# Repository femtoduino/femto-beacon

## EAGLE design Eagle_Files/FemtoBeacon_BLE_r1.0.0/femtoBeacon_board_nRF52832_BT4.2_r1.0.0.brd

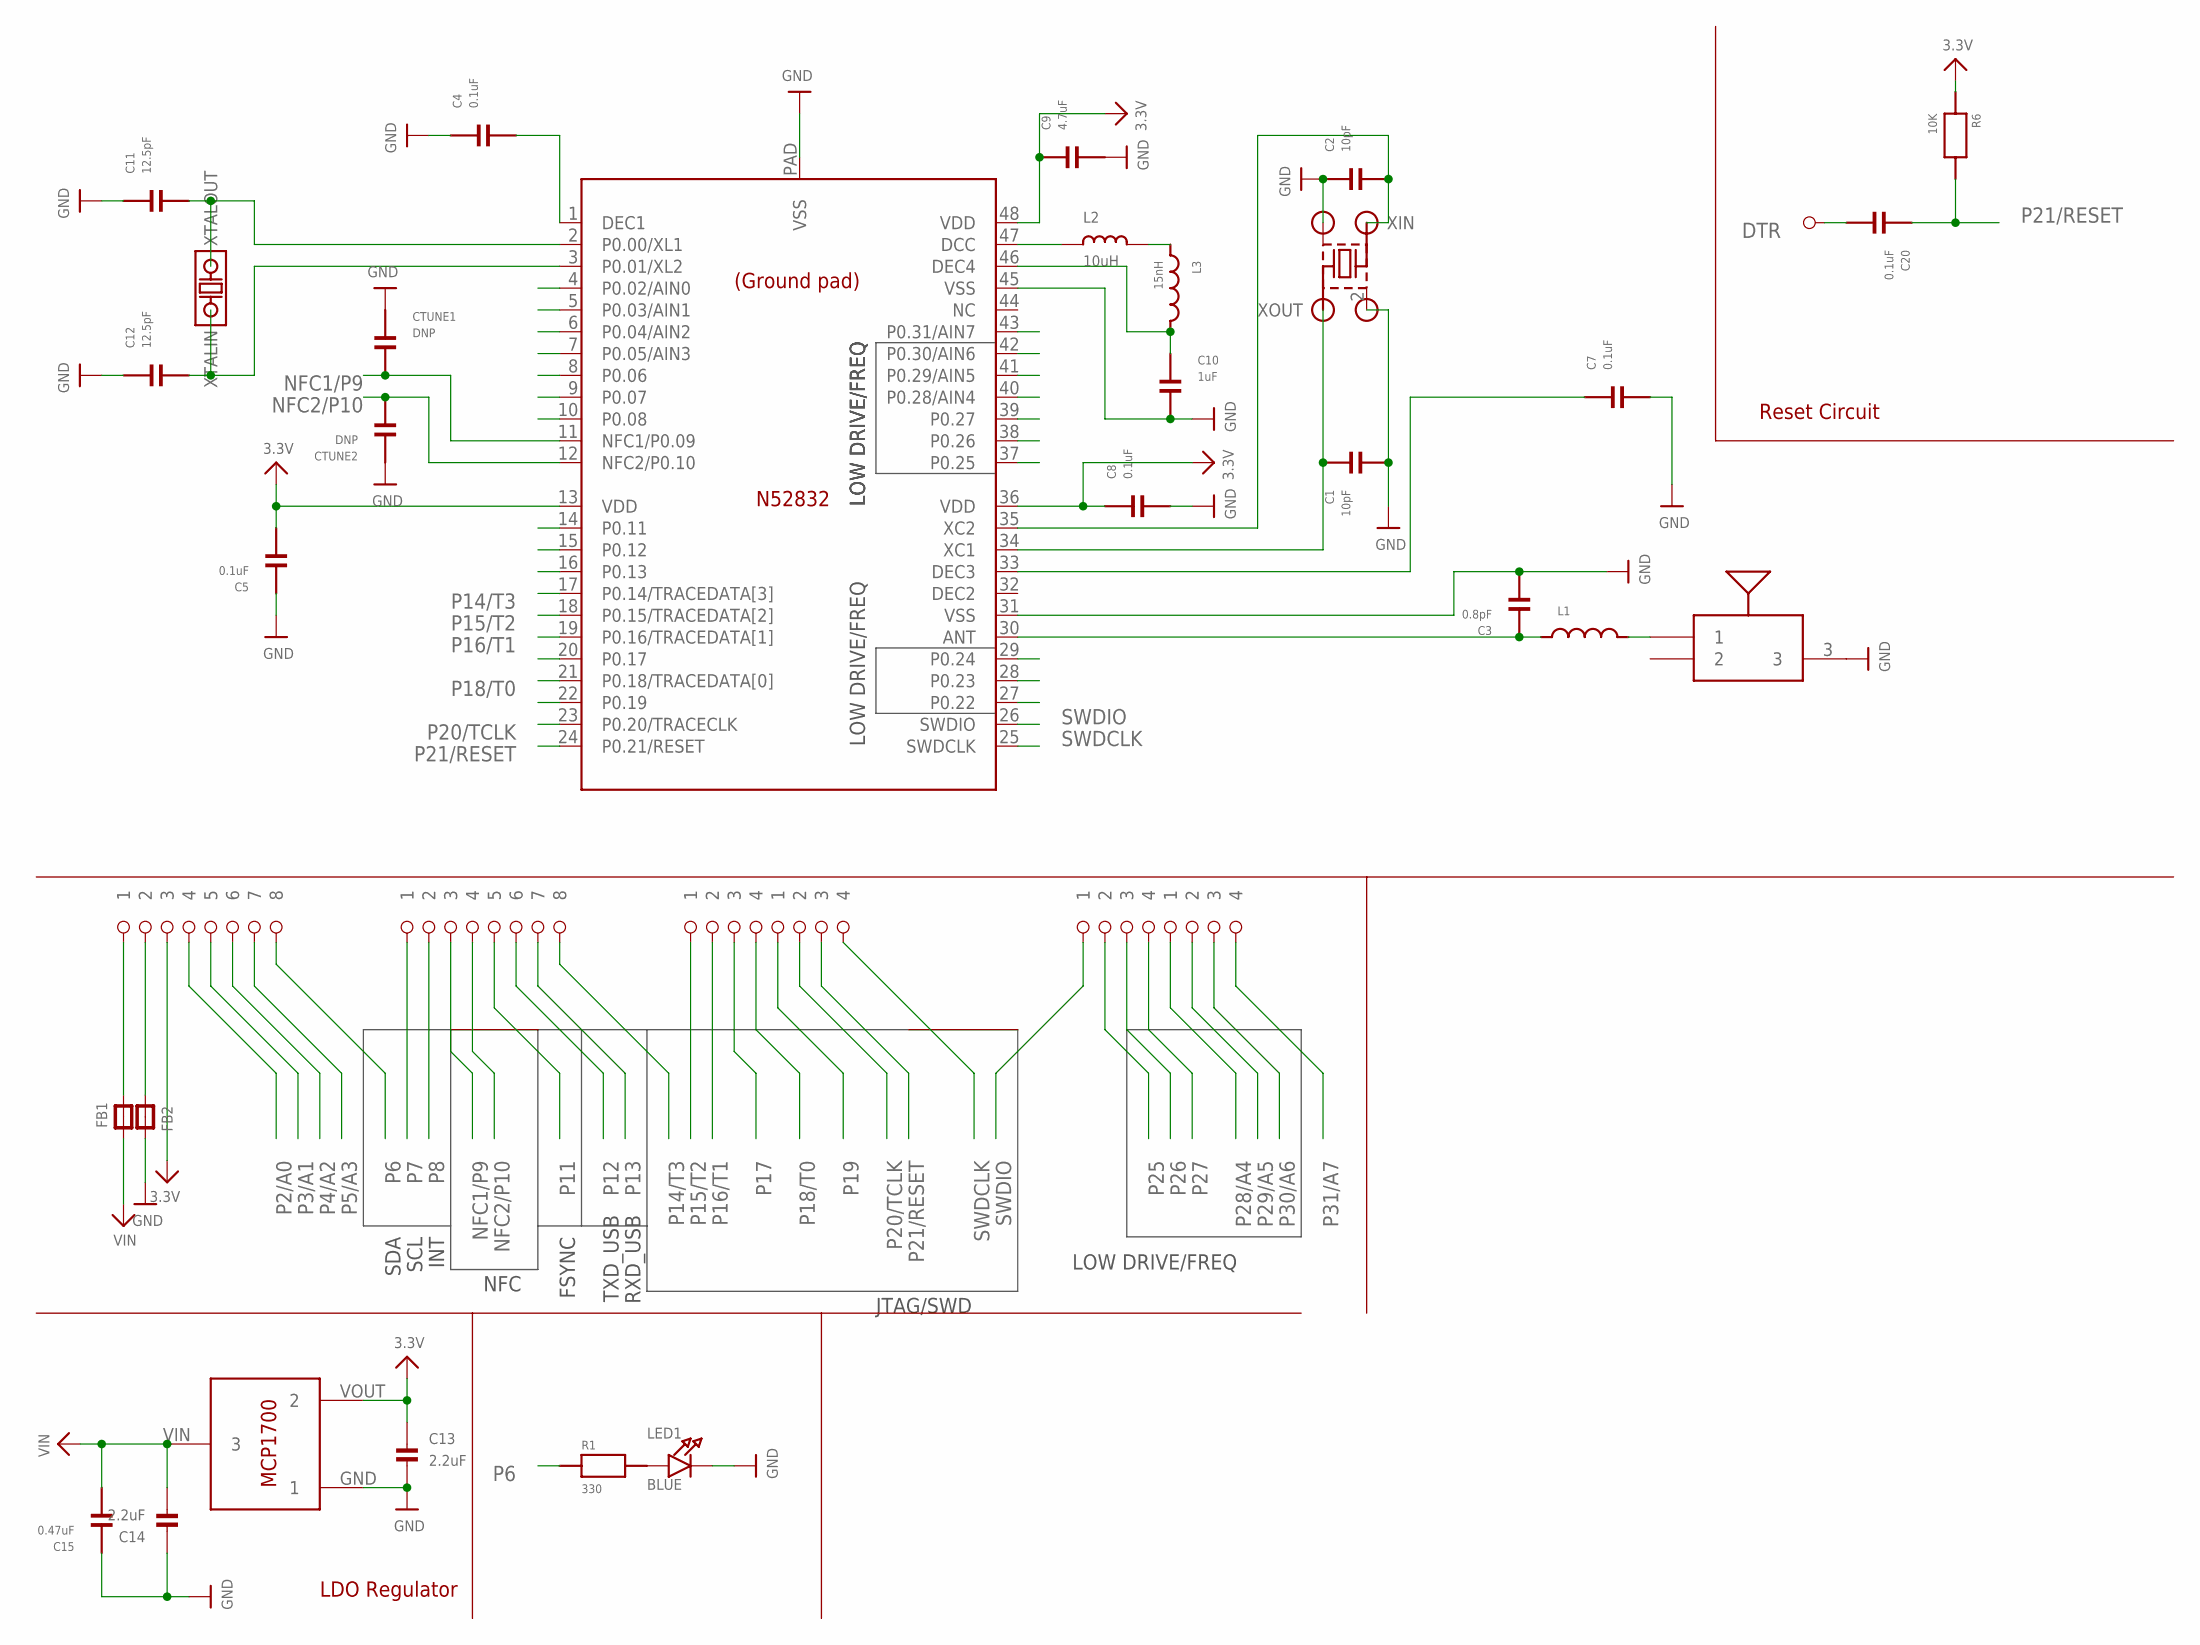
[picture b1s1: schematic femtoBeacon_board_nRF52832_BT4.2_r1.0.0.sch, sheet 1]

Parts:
ANTBAR: PULSE_ANT_2.4GHZ; ANT_BAR
C1, C2: 10pF; PART
C3: 0.8pF; PART
C4, C5, C7, C8, C20: 0.1uF; PART
C9: 4.7uF; PART
C10: 1uF; PART
C11, C12: 12.5pF; PART
C13, C14: 2.2uF; _0402MP
C15: 0.47uF; PART
CTUNE1, CTUNE2: DNP; PART
FB1, FB2: FERRITE_0603MP; _0603MP
IC1: NRF52832_QFN48; QFN48
L1: INDUCTOR_FIXED_0201; PART
L2: 10uH; _0603MP
L3: 15nH; PART
LED1: BLUE; CHIPLED_0603_NOOUTLINE
PIN4: 1X1_ROUND
PINS1, PINS2: 1X8_ROUND
PINS3A, PINS3B, PINS4A, PINS4B: 1X4_ROUND
R1: 330; PART
R6: 10K; PART
U$4: MCP1700T-3302E/TT
U$53: ABS06-107-32.768KHZ-T
XTAL: 32MHz; ABM11

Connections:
3.3V: C5.2, C8.1, C9.1, C13.1, IC1.13 (VDD), IC1.36 (VDD), IC1.48 (VDD), PINS1.P$3 (3), R6.1, U$4.VOUT (2); also elsewhere on the board
DTR: C20.2, PIN4.P$1
GND: ANTBAR.3, C1.2, C2.1, C3.2, C4.1, C5.1, C7.2, C8.2, C9.2, C10.2, C11.1, C12.1, C13.2, C14.1, C15.1, CTUNE1.1, CTUNE2.1, FB2.2, IC1.31 (VSS), IC1.45 (VSS), IC1.PAD (VSS), LED1.C, U$4.GND (1), XTAL.2 (GND), XTAL.4 (GND); also elsewhere on the board
unnamed: C4.2, IC1.1 (DEC1)
unnamed: L2.2, L3.1
unnamed: IC1.47 (DCC), L2.1
unnamed: C7.1, IC1.33 (DEC3)
unnamed: FB2.1, PINS1.P$2 (2)
unnamed: C10.1, IC1.46 (DEC4), L3.2
unnamed: LED1.A, R1.2
unnamed: FB1.2, PINS1.P$1 (1)
unnamed: C3.1, IC1.30 (ANT), L1.1
NFC1/P9: CTUNE1.2, IC1.11 (NFC1/P0.09), PINS2.P$3 (3)
NFC2/P10: CTUNE2.2, IC1.12 (NFC2/P0.10), PINS2.P$4 (4)
P0/XIN32: C11.2, IC1.2 (P0.00/XL1), U$53.2 (XTALOUT)
P1/XOUT32: C12.2, IC1.3 (P0.01/XL2), U$53.1 (XTALIN)
P2/A0: IC1.4 (P0.02/AIN0), PINS1.P$4 (4)
P3/A1: IC1.5 (P0.03/AIN1), PINS1.P$5 (5)
P4/A2: IC1.6 (P0.04/AIN2), PINS1.P$6 (6)
P5/A3: IC1.7 (P0.05/AIN3), PINS1.P$7 (7)
P6: IC1.8 (P0.06), PINS1.P$8 (8), R1.1; also elsewhere on the board
P7: IC1.9 (P0.07), PINS2.P$1 (1); also elsewhere on the board
P8: IC1.10 (P0.08), PINS2.P$2 (2); also elsewhere on the board
P11: IC1.14 (P0.11), PINS2.P$5 (5); also elsewhere on the board
P12: IC1.15 (P0.12), PINS2.P$6 (6)
P13: IC1.16 (P0.13), PINS2.P$7 (7)
P14/T3: IC1.17 (P0.14/TRACEDATA[3]), PINS2.P$8 (8)
P15/T2: IC1.18 (P0.15/TRACEDATA[2]), PINS3A.P$1 (1)
P16/T1: IC1.19 (P0.16/TRACEDATA[1]), PINS3A.P$2 (2)
P17: IC1.20 (P0.17), PINS3A.P$3 (3)
P18/T0: IC1.21 (P0.18/TRACEDATA[0]), PINS3A.P$4 (4)
P19: IC1.22 (P0.19), PINS3B.P$1 (1)
P20/TCLK: IC1.23 (P0.20/TRACECLK), PINS3B.P$2 (2)
P21/RESET: C20.1, IC1.24 (P0.21/RESET), PINS3B.P$3 (3), R6.2
P22: IC1.27 (P0.22)
P23: IC1.28 (P0.23)
P24: IC1.29 (P0.24)
P25: IC1.37 (P0.25), PINS4A.P$2 (2)
P26: IC1.38 (P0.26), PINS4A.P$3 (3)
P27: IC1.39 (P0.27), PINS4A.P$4 (4)
P28/A4: IC1.40 (P0.28/AIN4), PINS4B.P$1 (1)
P29/A5: IC1.41 (P0.29/AIN5), PINS4B.P$2 (2)
P30/A6: IC1.42 (P0.30/AIN6), PINS4B.P$3 (3)
P31/A7: IC1.43 (P0.31/AIN7), PINS4B.P$4 (4)
RF: ANTBAR.1, L1.2
SWDCLK: IC1.25 (SWDCLK), PINS3B.P$4 (4)
SWDIO: IC1.26 (SWDIO), PINS4A.P$1 (1)
VIN: C14.2, C15.2, FB1.1, U$4.VIN (3)
XIN: C1.1, IC1.34 (XC1), XTAL.3 (XOUT)
XOUT: C2.2, IC1.35 (XC2), XTAL.1 (XIN)

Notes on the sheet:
LOW DRIVE/FREQ
SDA
SCL
INT
FSYNC
TXD_USB
RXD_USB
Reset Circuit
LDO Regulator
JTAG/SWD
NFC

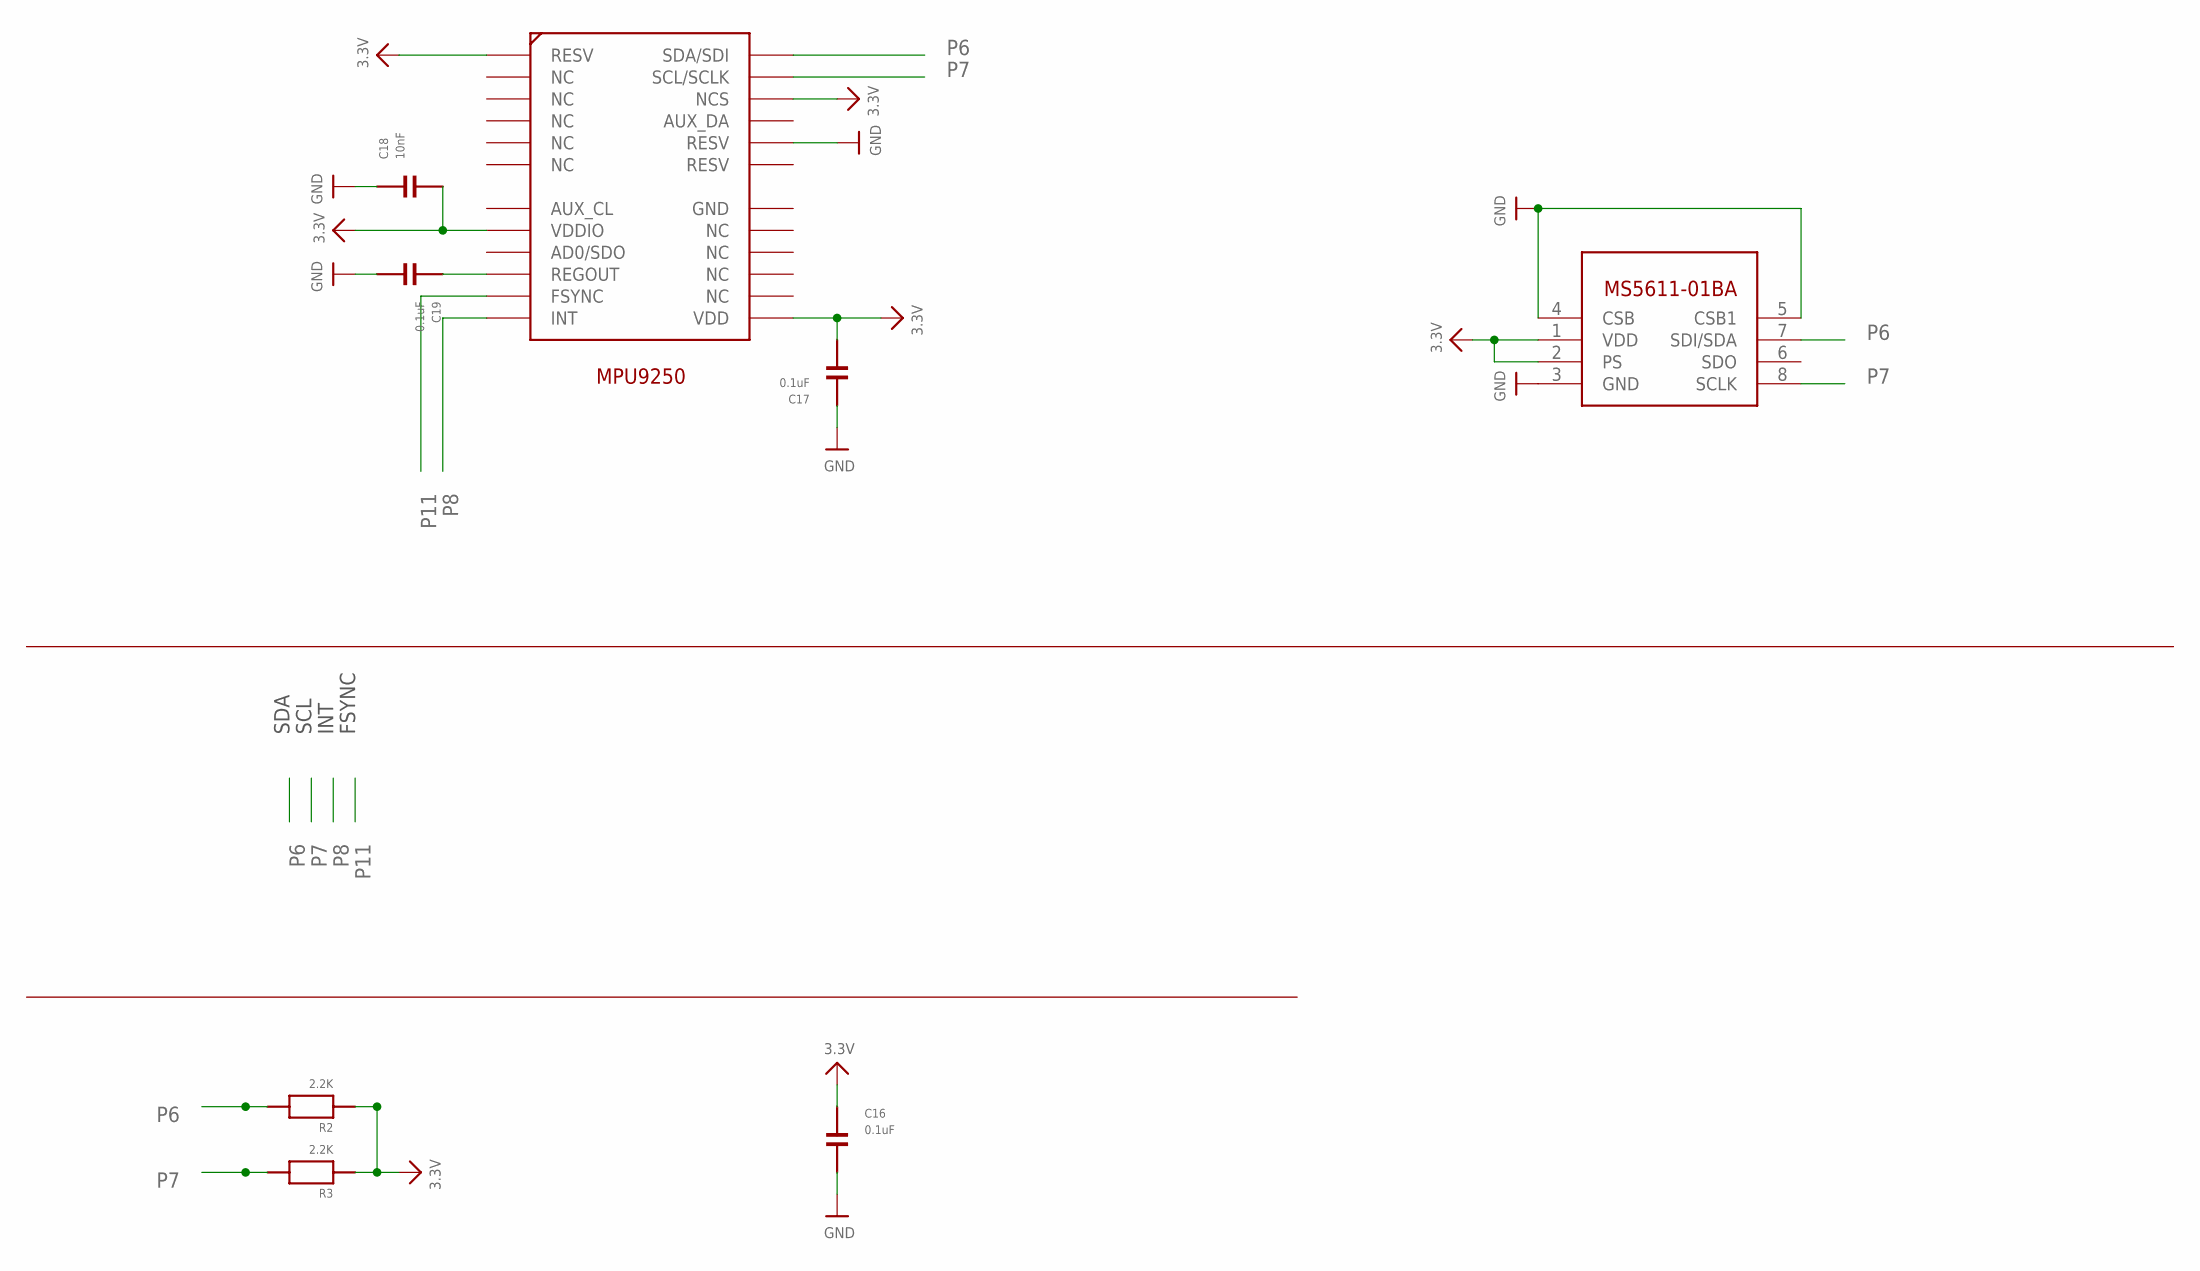
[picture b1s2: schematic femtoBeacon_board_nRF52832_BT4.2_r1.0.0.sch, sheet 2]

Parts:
BARO1: MS5611-01BA03
C16, C17, C19: 0.1uF; PART
C18: 10nF; PART
IMU1: MPU-9250; QFN_3X3MM
R2, R3: 2.2K; PART

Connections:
3.3V: BARO1.1 (VDD), BARO1.2 (PS), C16.1, C17.2, C18.2, IMU1.P$1 (RESV), IMU1.P$8 (VDDIO), IMU1.P$13 (VDD), IMU1.P$22 (NCS), R2.1, R3.1; also elsewhere on the board
GND: BARO1.3 (GND), BARO1.4 (CSB), BARO1.5 (CSB1), C16.2, C17.1, C18.1, C19.2, IMU1.P$20 (RESV); also elsewhere on the board
P6: BARO1.7 (SDI/SDA), IMU1.P$24 (SDA/SDI), R2.2; also elsewhere on the board
P7: BARO1.8 (SCLK), IMU1.P$23 (SCL/SCLK), R3.2; also elsewhere on the board
P8: IMU1.P$12 (INT); also elsewhere on the board
P11: IMU1.P$11 (FSYNC); also elsewhere on the board
REGOUT: C19.1, IMU1.P$10 (REGOUT)

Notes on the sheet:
MPU9250
SDA
SCL
INT
FSYNC

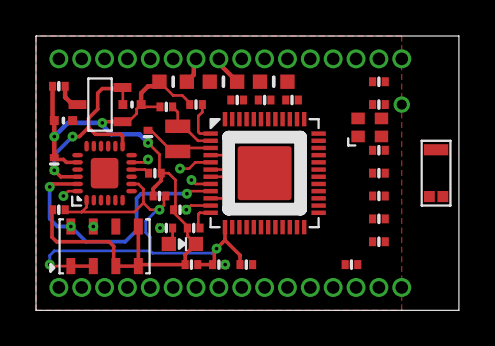
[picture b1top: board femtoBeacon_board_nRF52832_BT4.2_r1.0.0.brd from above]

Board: 4 copper layers, 23.5 x 15.2 mm, 45 parts (0 on the bottom side), 48 nets.

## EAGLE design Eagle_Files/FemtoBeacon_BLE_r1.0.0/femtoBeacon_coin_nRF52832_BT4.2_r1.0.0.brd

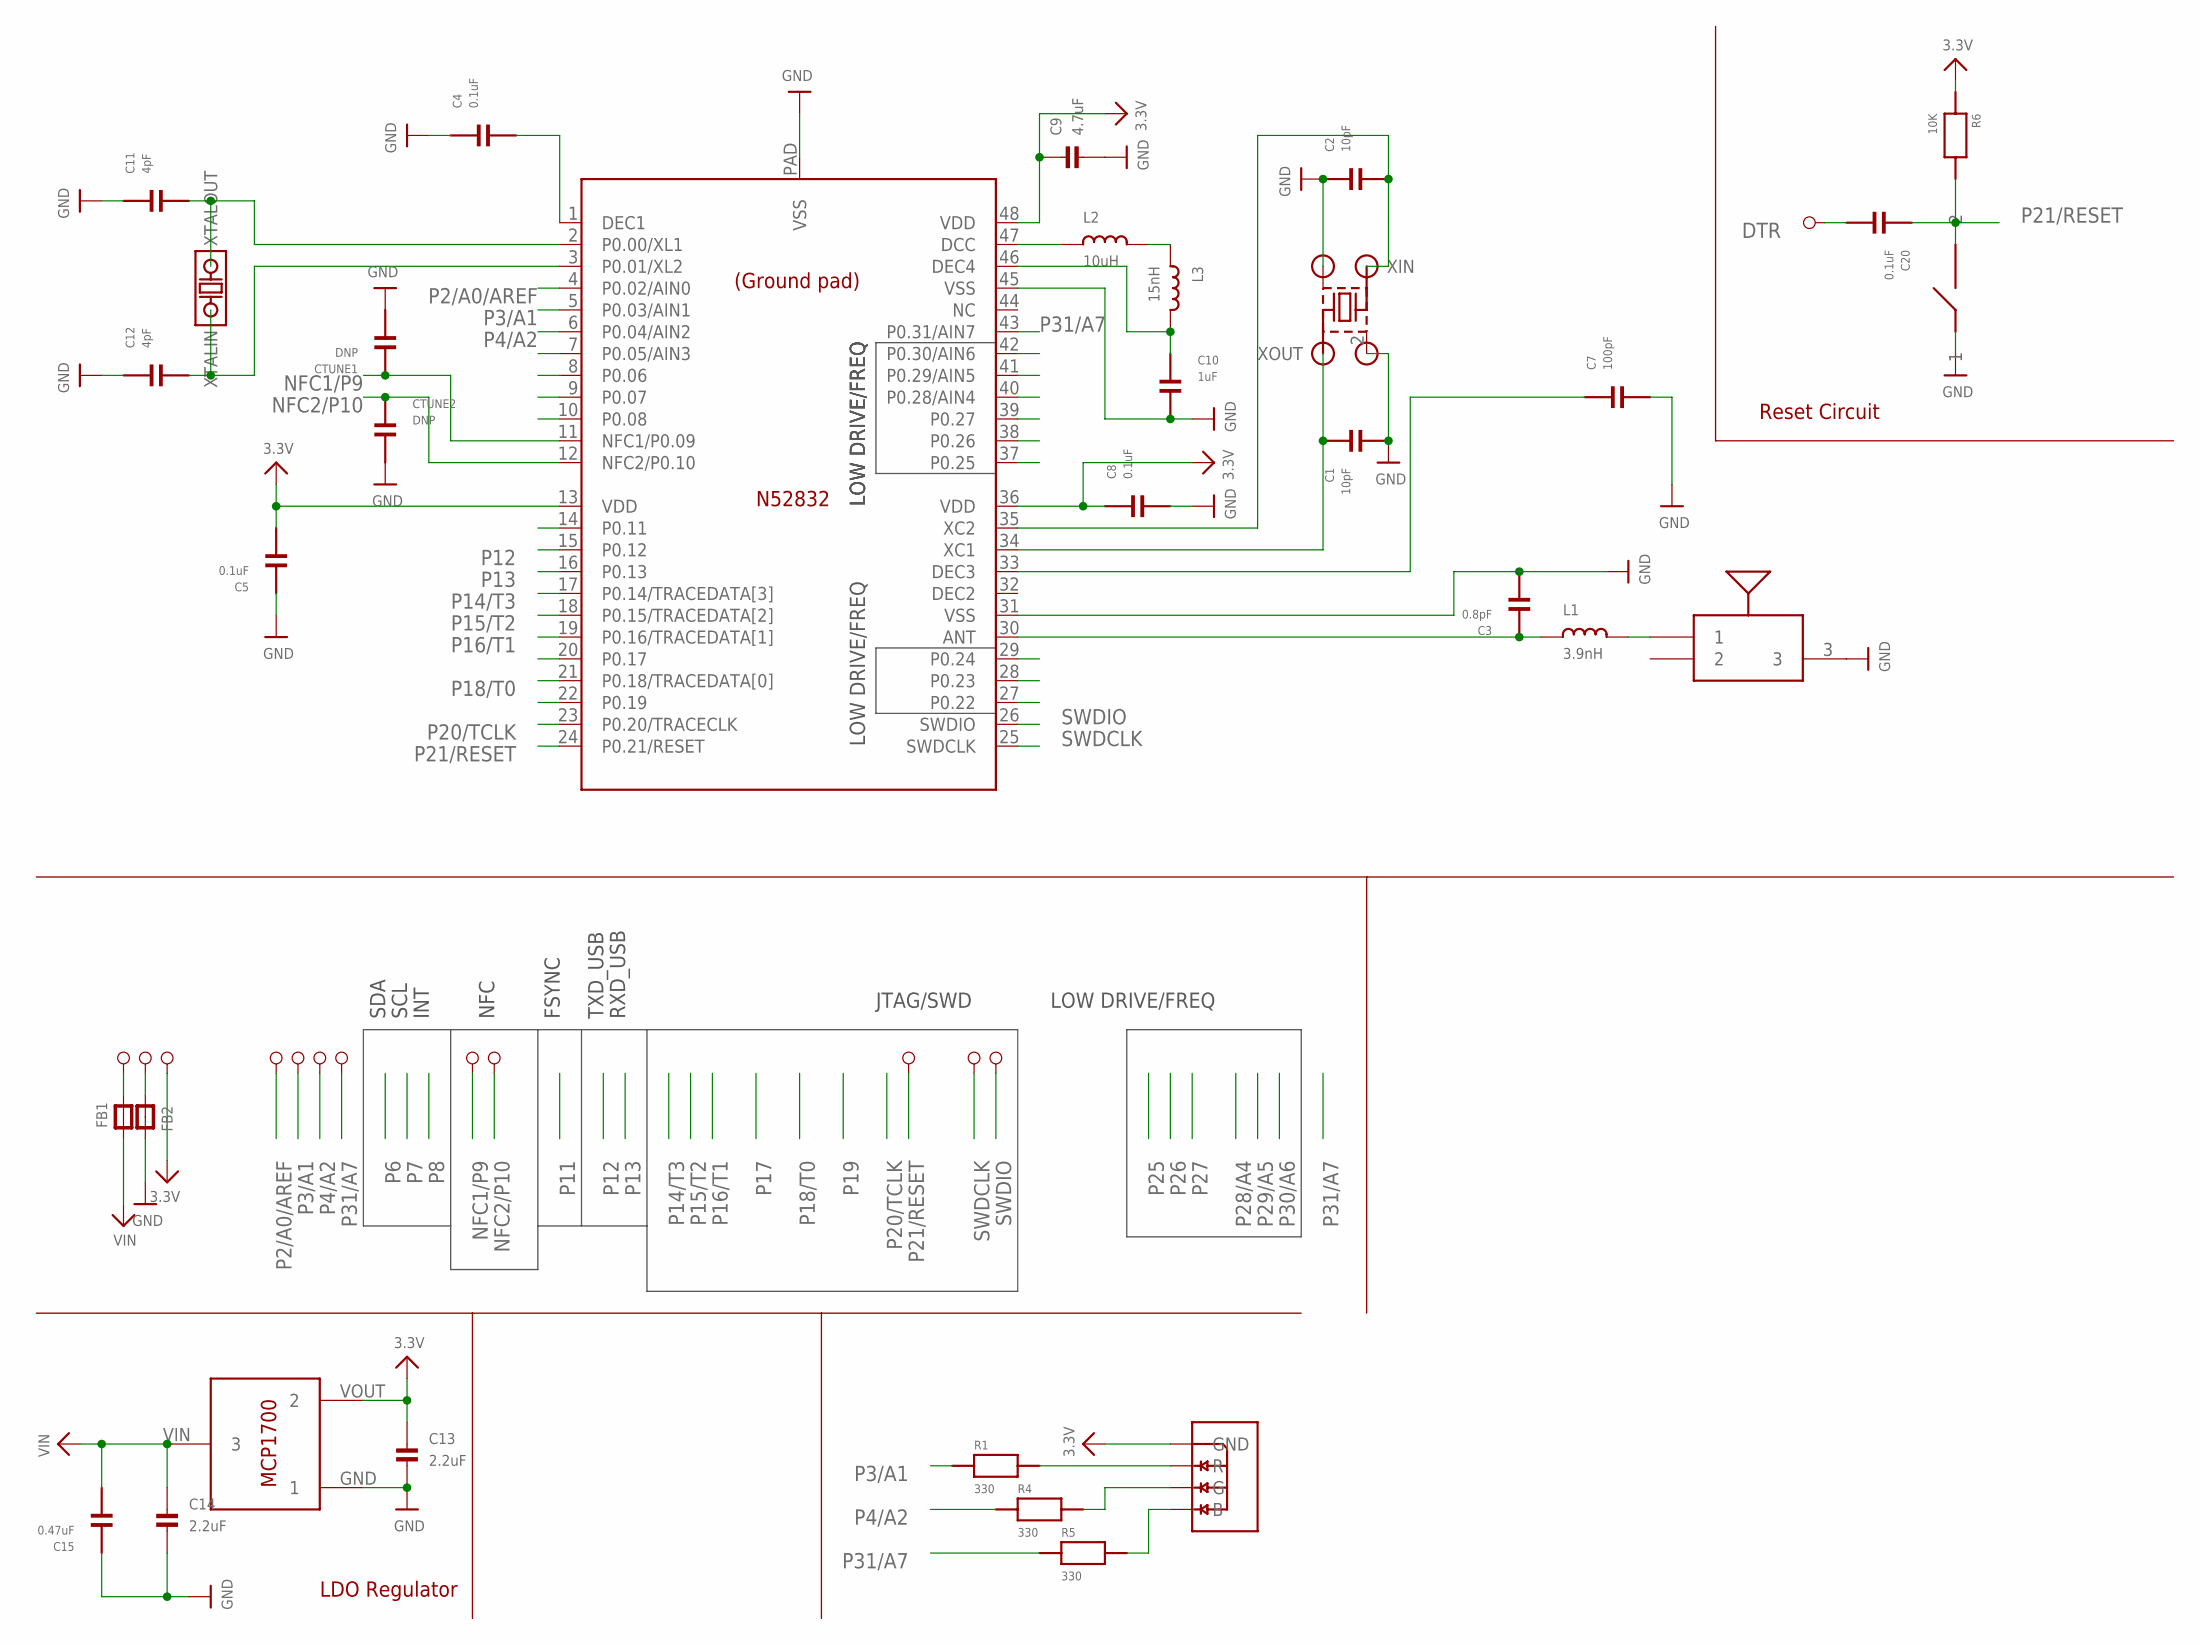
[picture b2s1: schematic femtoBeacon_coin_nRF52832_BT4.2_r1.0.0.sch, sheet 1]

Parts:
ANTBAR: PULSE_ANT_2.4GHZ; ANT_BAR
C1, C2: 10pF; PART
C3: 0.8pF; PART
C4, C5, C8, C20: 0.1uF; PART
C7: 100pF; PART
C9: 4.7uF; _0402MP
C10: 1uF; PART
C11, C12: 4pF; PART
C13, C14: 2.2uF; _0402MP
C15: 0.47uF; PART
CTUNE1, CTUNE2: DNP; PART
FB1, FB2: FERRITE_0603MP; _0603MP
IC1: NRF52832_QFN48; QFN48
L1: 3.9nH; _0402MP
L2: 10uH; _0603MP
L3: 15nH; _0402MP
LDO_VREG: MCP1700T-3302E/TT
LED1: LRTB_R48G
PIN1, PIN2, PIN3, PIN4, PIN7, PIN8, PIN9, PIN10, PIN13, PIN14, PIN25, PIN26, PIN27: 1X1_ROUND
R1, R4, R5: 330; PART
R6: 10K; PART
RESET_JMP: SPST_SMD
XOSC32K: ABS06-107-32.768KHZ-T
XTAL: 32MHz; ABM11

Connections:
3.3V: C5.2, C8.1, C9.1, C13.1, IC1.13 (VDD), IC1.36 (VDD), IC1.48 (VDD), LDO_VREG.VOUT (2), LED1.1 (GND), PIN3.P$1, R6.1; also elsewhere on the board
B: LED1.4 (B), R5.2
DTR: C20.2, PIN4.P$1
G: LED1.3 (G), R4.2
GND: ANTBAR.3, C1.2, C2.1, C3.2, C4.1, C5.1, C7.2, C8.2, C9.2, C10.2, C11.1, C12.1, C13.2, C14.2, C15.1, CTUNE1.2, CTUNE2.2, FB2.2, IC1.31 (VSS), IC1.45 (VSS), IC1.PAD (VSS), LDO_VREG.GND (1), RESET_JMP.1, XTAL.2 (GND), XTAL.4 (GND); also elsewhere on the board
unnamed: C4.2, IC1.1 (DEC1)
unnamed: L2.2, L3.1
unnamed: IC1.47 (DCC), L2.1
unnamed: C7.1, IC1.33 (DEC3)
unnamed: FB2.1, PIN2.P$1
unnamed: C10.1, IC1.46 (DEC4), L3.2
unnamed: FB1.2, PIN1.P$1
unnamed: C3.1, IC1.30 (ANT), L1.1
NFC1/P9: CTUNE1.1, IC1.11 (NFC1/P0.09), PIN13.P$1
NFC2/P10: CTUNE2.1, IC1.12 (NFC2/P0.10), PIN14.P$1
P0/XIN32: C11.2, IC1.2 (P0.00/XL1), XOSC32K.2 (XTALOUT)
P1/XOUT32: C12.2, IC1.3 (P0.01/XL2), XOSC32K.1 (XTALIN)
P2/A0/AREF: IC1.4 (P0.02/AIN0), PIN9.P$1
P3/A1: IC1.5 (P0.03/AIN1), PIN10.P$1, R1.1
P4/A2: IC1.6 (P0.04/AIN2), PIN7.P$1, R4.1
P5/A3: IC1.7 (P0.05/AIN3)
P6: IC1.8 (P0.06); also elsewhere on the board
P7: IC1.9 (P0.07); also elsewhere on the board
P8: IC1.10 (P0.08); also elsewhere on the board
P11: IC1.14 (P0.11); also elsewhere on the board
P12: IC1.15 (P0.12)
P13: IC1.16 (P0.13)
P14/T3: IC1.17 (P0.14/TRACEDATA[3])
P15/T2: IC1.18 (P0.15/TRACEDATA[2])
P16/T1: IC1.19 (P0.16/TRACEDATA[1])
P17: IC1.20 (P0.17)
P18/T0: IC1.21 (P0.18/TRACEDATA[0])
P19: IC1.22 (P0.19)
P20/TCLK: IC1.23 (P0.20/TRACECLK)
P21/RESET: C20.1, IC1.24 (P0.21/RESET), PIN25.P$1, R6.2, RESET_JMP.2
P22: IC1.27 (P0.22)
P23: IC1.28 (P0.23)
P24: IC1.29 (P0.24)
P25: IC1.37 (P0.25)
P26: IC1.38 (P0.26)
P27: IC1.39 (P0.27)
P28/A4: IC1.40 (P0.28/AIN4)
P29/A5: IC1.41 (P0.29/AIN5)
P30/A6: IC1.42 (P0.30/AIN6)
P31/A7: IC1.43 (P0.31/AIN7), PIN8.P$1, R5.1
R: LED1.2 (R), R1.2
RF: ANTBAR.1, L1.2
SWDCLK: IC1.25 (SWDCLK), PIN26.P$1
SWDIO: IC1.26 (SWDIO), PIN27.P$1
VIN: C14.1, C15.2, FB1.1, LDO_VREG.VIN (3)
XIN: C1.1, IC1.34 (XC1), XTAL.3 (XOUT)
XOUT: C2.2, IC1.35 (XC2), XTAL.1 (XIN)

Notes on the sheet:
LOW DRIVE/FREQ
SDA
SCL
INT
FSYNC
TXD_USB
RXD_USB
Reset Circuit
LDO Regulator
JTAG/SWD
NFC

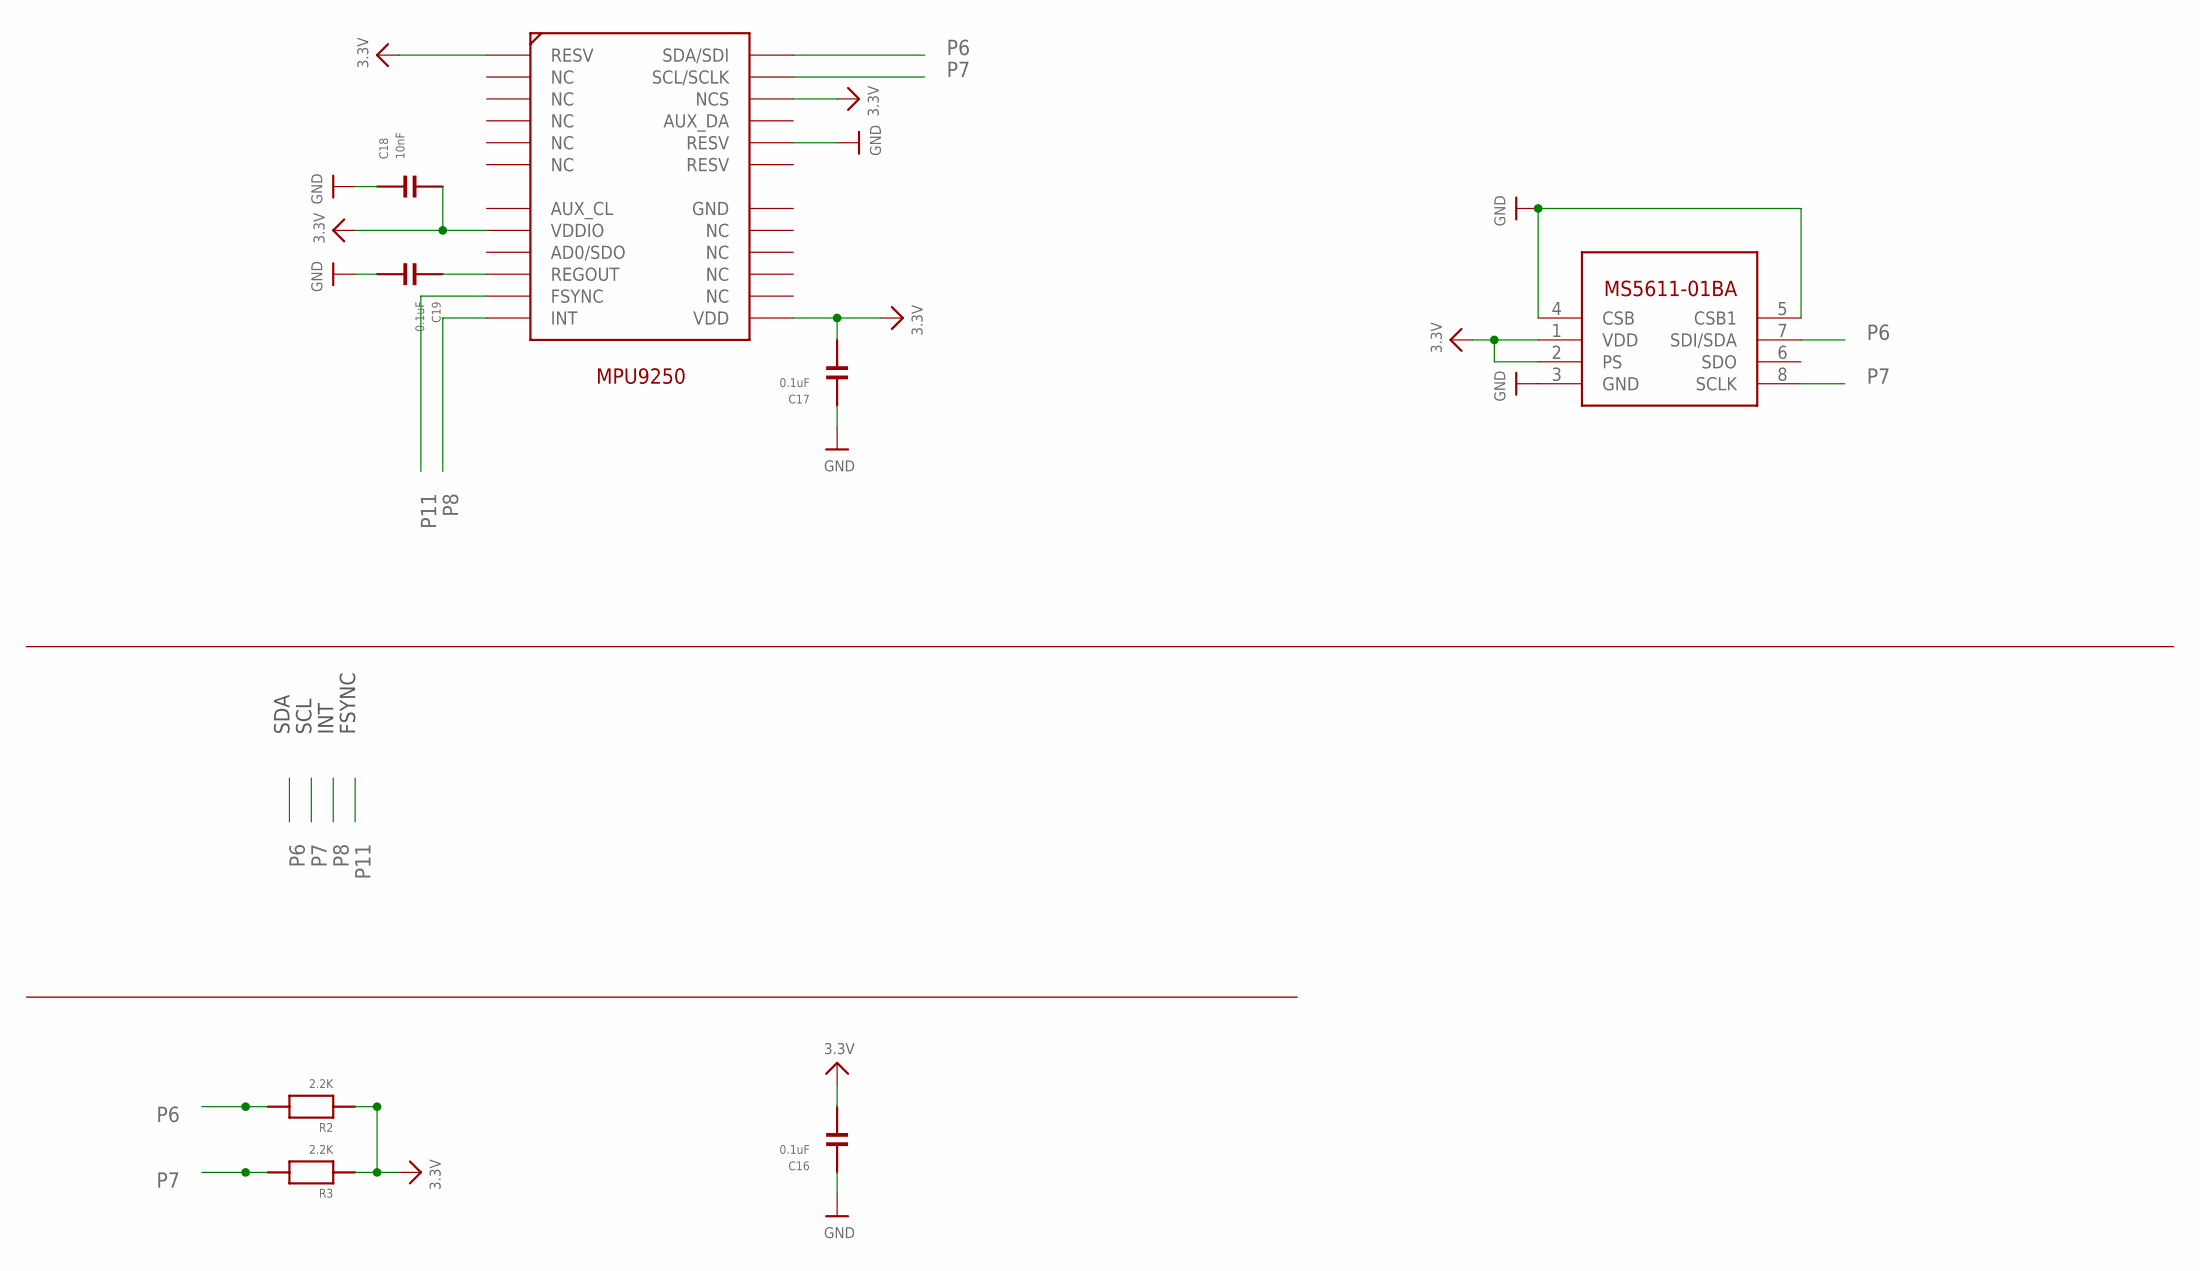
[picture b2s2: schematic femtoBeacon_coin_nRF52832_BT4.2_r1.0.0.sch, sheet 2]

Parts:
BARO1: MS5611-01BA03
C16, C17, C19: 0.1uF; PART
C18: 10nF; PART
IMU1: MPU-9250; QFN_3X3MM
R2, R3: 2.2K; PART

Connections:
3.3V: BARO1.1 (VDD), BARO1.2 (PS), C16.2, C17.2, C18.2, IMU1.P$1 (RESV), IMU1.P$8 (VDDIO), IMU1.P$13 (VDD), IMU1.P$22 (NCS), R2.1, R3.1; also elsewhere on the board
GND: BARO1.3 (GND), BARO1.4 (CSB), BARO1.5 (CSB1), C16.1, C17.1, C18.1, C19.2, IMU1.P$20 (RESV); also elsewhere on the board
P6: BARO1.7 (SDI/SDA), IMU1.P$24 (SDA/SDI), R2.2; also elsewhere on the board
P7: BARO1.8 (SCLK), IMU1.P$23 (SCL/SCLK), R3.2; also elsewhere on the board
P8: IMU1.P$12 (INT); also elsewhere on the board
P11: IMU1.P$11 (FSYNC); also elsewhere on the board
REGOUT: C19.1, IMU1.P$10 (REGOUT)

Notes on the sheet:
MPU9250
SDA
SCL
INT
FSYNC

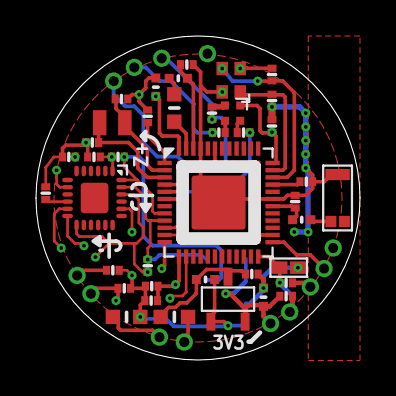
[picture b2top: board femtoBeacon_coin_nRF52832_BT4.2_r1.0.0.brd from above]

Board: 4 copper layers, 18.0 x 18.0 mm, 54 parts (1 on the bottom side), 34 nets.

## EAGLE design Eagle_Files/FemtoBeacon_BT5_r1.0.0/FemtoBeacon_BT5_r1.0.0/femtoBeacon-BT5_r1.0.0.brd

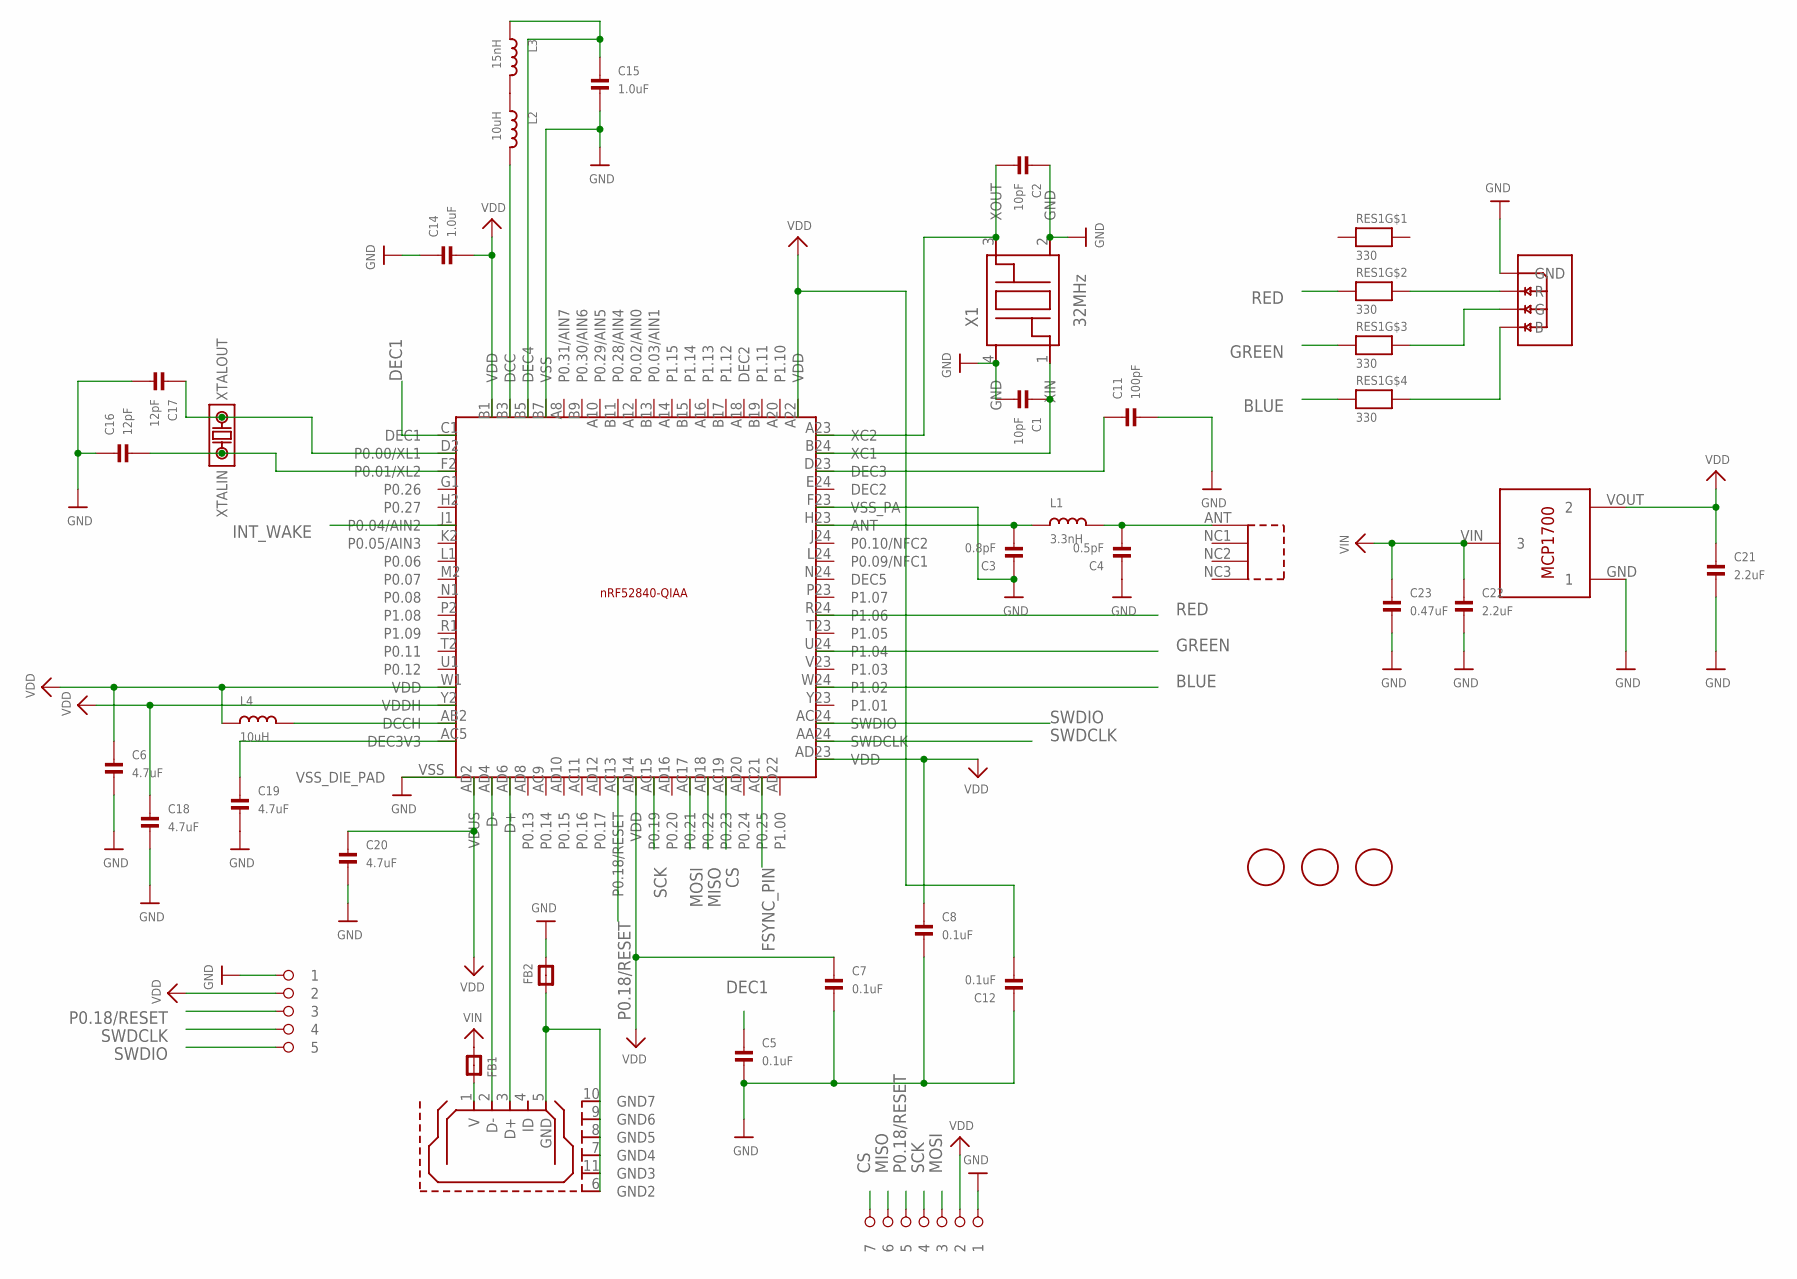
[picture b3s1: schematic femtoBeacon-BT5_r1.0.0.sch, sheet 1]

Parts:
ANT: 0479480001
C1, C2: 10pF; _0402MP
C3: 0.8pF; _0402MP
C4: 0.5pF; _0402MP
C5, C7, C8, C12: 0.1uF; _0402MP
C6, C18, C19, C20: 4.7uF; _0402MP
C11: 100pF; _0402MP
C14, C15: 1.0uF; _0402MP
C16, C17: 12pF; _0402MP
C21, C22: 2.2uF; _0402MP
C23: 0.47uF; _0402MP
FB1, FB2: FERRITE_0603MP; _0603MP
FID1, FID2, FID3: FIDUCIAL; FIDUCIAL_1MM
IC: NRF52840
L1: 3.3nH; _0402MP
L2, L4: 10uH; _0402MP
L3: 15nH; _0402MP
LDO_VREG: MCP1700T-3302E/TT
RES1: 330; RESPACK_4X0603
U$1: 1X5_ROUND
U$7: LRTB_R48G
U$27: 1X7_ROUND
USB: USB_MICROB; USB_MICROB_PACKAGE
X1: 32MHz; FA-128
X2: 32.768kHZ; ABS06-107-32.768KHZ-T

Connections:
ANT: C3.2, IC.H23 (ANT), L1.1
BLUE: IC.W24 (P1.02), RES1.4 (1)
CS: IC.AC19 (P0.23), U$27.P$7 (7); also elsewhere on the board
D23: C11.1, IC.D23 (DEC3)
DCCH: IC.AB2 (DCCH), L4.2
DEC1: C5.1, IC.C1 (DEC1)
DEC3V3: C19.1, IC.AC5 (DEC3V3)
FSYNC_PIN: IC.AC21 (P0.25); also elsewhere on the board
GND: C1.2, C2.1, C3.1, C4.1, C5.2, C6.2, C7.2, C8.2, C11.2, C12.1, C14.1, C15.2, C16.1, C17.2, C18.2, C19.2, C20.2, C21.2, C22.2, C23.2, FB2.2, IC.B7 (VSS), IC.F23 (VSS_PA), IC.VSS (VSS_DIE_PAD), LDO_VREG.GND (1), U$1.P$1 (1), U$7.1 (GND), U$27.P$1 (1), X1.2 (GND), X1.4 (GND); also elsewhere on the board
GND_IN: FB2.1, USB.5 (GND), USB.6 (GND2), USB.7 (GND4), USB.8 (GND5), USB.9 (GND6), USB.10 (GND7), USB.11 (GND3)
GREEN: IC.U24 (P1.04), RES1.3 (1)
INT_WAKE: IC.J1 (P0.04/AIN2); also elsewhere on the board
MISO: IC.AD18 (P0.22), U$27.P$6 (6); also elsewhere on the board
MOSI: IC.AC17 (P0.21), U$27.P$3 (3); also elsewhere on the board
unnamed: FB1.2, USB.1 (V)
unnamed: RES1.5 (2), U$7.4 (B)
unnamed: RES1.6 (2), U$7.3 (G)
unnamed: RES1.7 (2), U$7.2 (R)
unnamed: IC.B3 (DCC), L2.2
unnamed: L2.1, L3.2
unnamed: C15.1, IC.B5 (DEC4), L3.1
P0.18/RESET: IC.AC13 (P0.18/RESET), U$1.P$3 (3), U$27.P$5 (5)
RED: IC.R24 (P1.06), RES1.2 (1)
RF: ANT.ANT (1), C4.2, L1.2
SCK: IC.AC15 (P0.19), U$27.P$4 (4); also elsewhere on the board
SWDCLK: IC.AA24 (SWDCLK), U$1.P$4 (4)
SWDIO: IC.AC24 (SWDIO), U$1.P$5 (5)
USB_DM: IC.AD4 (D-), USB.2 (D-)
USB_DP: IC.AD6 (D+), USB.3 (D+)
VDD: C6.1, C7.1, C8.1, C12.2, C14.2, C18.1, C20.1, C21.1, IC.A22 (VDD), IC.AD2 (VBUS), IC.AD14 (VDD), IC.AD23 (VDD), IC.B1 (VDD), IC.W1 (VDD), IC.Y2 (VDDH), L4.1, LDO_VREG.VOUT (2), U$1.P$2 (2), U$27.P$2 (2); also elsewhere on the board
VIN: C22.1, C23.1, FB1.1, LDO_VREG.VIN (3)
XC1: C1.1, IC.B24 (XC1), X1.1 (XIN)
XC2: C2.2, IC.A23 (XC2), X1.3 (XOUT)
XL1: C17.1, IC.D2 (P0.00/XL1), X2.2 (XTALOUT)
XL2: C16.2, IC.F2 (P0.01/XL2), X2.1 (XTALIN)

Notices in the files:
parts and their libraries:
microbuilder: This work is placed in the public domain, and may be freely used for commercial and non-commercial work with the following conditions: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
